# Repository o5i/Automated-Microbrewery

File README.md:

# Automated-Microbrewery

This is a small hobby/micro brewery based on herms system. i have created for friends.
The setup appart of the work i spend has a good price/quality value. 
In all i spent about 800€ for the hardware.
The controller is made of a raspberry pi (debian linux) interfaced whit a Teensy (Arduino based Microcontroller). 
The program runs on codesys, codesys is a  IEC 61131-3 runtime that allows me to use standard plc programing languages. 
I decided to use the pi because it is possible to interface whit a lot of cheap hardware like the multitouch screen.
The other point is that you have access to the network/internet and you can implement a webinterface or other remote management.
The controller box is made from lasercutted wood.
The gas burners came from old wrecked gas heaters.

Here you can see the controler in action:

https://www.youtube.com/watch?v=9Vse3HxLSbY

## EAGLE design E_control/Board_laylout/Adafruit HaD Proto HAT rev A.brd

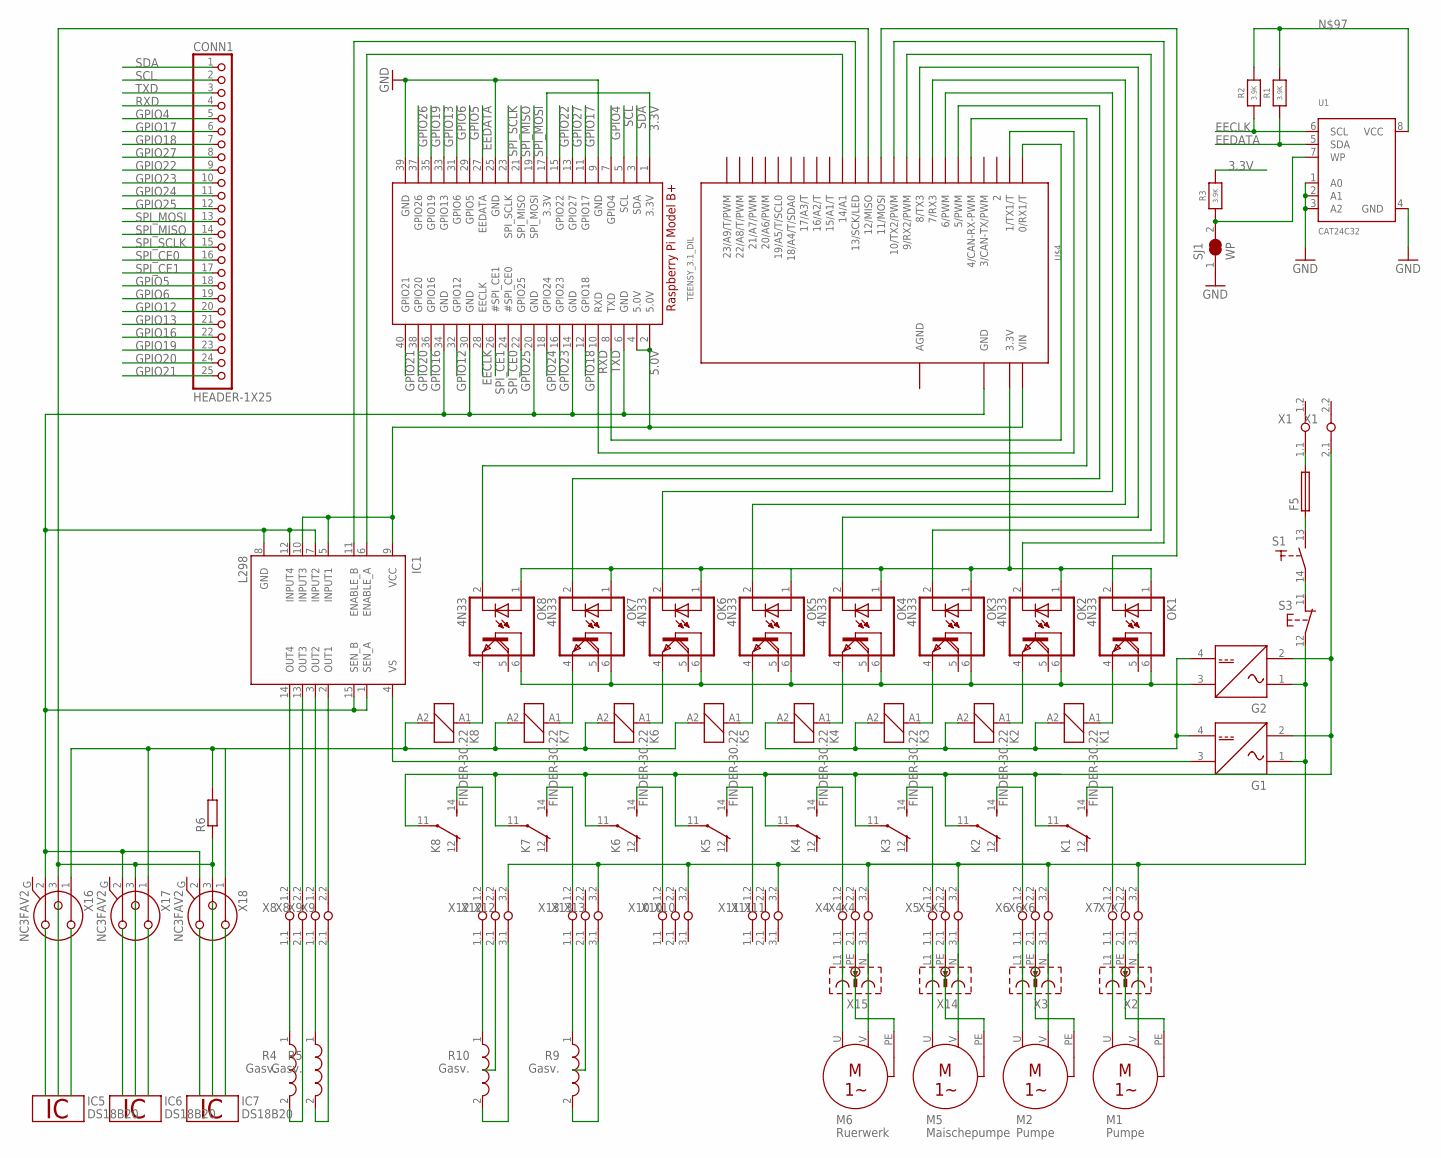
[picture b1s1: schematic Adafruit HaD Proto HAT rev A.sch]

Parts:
CONN1: HEADER-1X25; 1X25_ROUND_70MIL
F5: KS9V
G1, G2: NETZTEIL_GLEICHSPANNUNG
IC1: L298; MULTIWATT-15
IC5, IC6, IC7: DS18B20; TO92-
K1, K2, K3, K4, K5, K6, K7, K8: FINDER-30.22
M1, M2: Pumpe; MOTOR_1-PHASEN
M5: Maischepumpe; MOTOR_1-PHASEN
M6: Ruerwerk; MOTOR_1-PHASEN
OK1, OK2, OK3, OK4, OK5, OK6, OK7, OK8: 4N33; DIL06
R1, R2, R3: 3.9K; 0805-NO
R4, R5, R9, R10: Gasv.; SPULE
R6: R-EU_0204/2V; 0204V
RPI1: RASPBERRYPI_BPLUS_HATNOSLOTS; PI_HAT_NOSLOTS
S1: SCHLIESSER_KIPPSCHALTER
S3: TASTER_OEFFNER; AUSTASTER
SJ1: WP; SOLDERJUMPER_CLOSEDWIRE
U1: CAT24C32; SOIC8_150MIL
U$4: TEENSY_3.1_DIL; TEENSY3-DIL
X1, X8, X9: KLEMME_1-2
X2, X3, X14, X15: STECKDOSE
X4, X5, X6, X7, X10, X11, X12, X13: KLEMME_1-3
X16, X17, X18: NC3FAV2

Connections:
1W: IC5.2 (1W), IC6.2 (1W), IC7.2 (1W)
3.3V: R3.2, RPI1.1 (3.3V), RPI1.17 (3.3V)
5.0V: IC1.5 (INPUT1), IC1.9 (VCC), IC1.10 (INPUT3), RPI1.2 (5.0V), RPI1.4 (5.0V), U$4.VIN
AGND: U$4.AGND
EECLK: R2.1, RPI1.28 (EECLK), U1.6 (SCL)
EEDATA: R1.1, RPI1.27 (EEDATA), U1.5 (SDA)
GND: IC1.1 (SEN_A), IC1.7 (INPUT2), IC1.8 (GND), IC1.12 (INPUT4), IC1.15 (SEN_B), IC5.1 (GND), IC6.1 (GND), IC7.1 (GND), RPI1.6 (GND), RPI1.9 (GND), RPI1.14 (GND), RPI1.20 (GND), RPI1.25 (GND), RPI1.30 (GND), RPI1.34 (GND), RPI1.39 (GND), SJ1.1, U1.1 (A0), U1.2 (A1), U1.3 (A2), U1.4 (GND), U$4.GND, X16.2, X17.2, X18.2
GPIO4: CONN1.5, RPI1.7 (GPIO4)
GPIO5: CONN1.18, RPI1.29 (GPIO5)
GPIO6: CONN1.19, RPI1.31 (GPIO6)
GPIO12: CONN1.20, RPI1.32 (GPIO12)
GPIO13: CONN1.21, RPI1.33 (GPIO13)
GPIO16: CONN1.22, RPI1.36 (GPIO16)
GPIO17: CONN1.6, RPI1.11 (GPIO17)
GPIO18: CONN1.7, RPI1.12 (GPIO18)
GPIO19: CONN1.23, RPI1.35 (GPIO19)
GPIO20: CONN1.24, RPI1.38 (GPIO20)
GPIO21: CONN1.25, RPI1.40 (GPIO21)
GPIO22: CONN1.9, RPI1.15 (GPIO22)
GPIO23: CONN1.10, RPI1.16 (GPIO23)
GPIO24: CONN1.11, RPI1.18 (GPIO24)
GPIO25: CONN1.12, RPI1.22 (GPIO25)
GPIO26: RPI1.37 (GPIO26)
GPIO27: CONN1.8, RPI1.13 (GPIO27)
unnamed: R3.1, SJ1.2, U1.7 (WP)
unnamed: IC1.11 (ENABLE_B), U$4.13 (13/SCK/LED)
unnamed: IC1.6 (ENABLE_A), U$4.14/A0 (14/A1)
unnamed: IC1.14 (OUT4), X8.1.2
unnamed: G1.3, IC1.4 (VS)
unnamed: G1.1, G1.2, G2.1, G2.2, S3.12 (2), X1.2.1, X4.3.2, X5.3.2, X6.3.2, X7.3.2, X10.3.2, X11.3.2, X12.3.2, X13.3.2
unnamed: R4.2, X8.2.1
unnamed: IC1.3 (OUT2), X9.1.2
unnamed: IC1.2 (OUT1), X9.2.2
unnamed: IC1.13 (OUT3), X8.2.2
unnamed: OK4.2 (C), U$4.8 (8/TX3)
unnamed: OK3.2 (C), U$4.9 (9/RX2/PWM)
unnamed: OK2.2 (C), U$4.10 (10/TX2/PWM)
unnamed: OK1.2 (C), U$4.11 (11/MOSI)
unnamed: G2.3, OK1.6 (B), OK2.6 (B), OK3.6 (B), OK4.6 (B), OK5.6 (B), OK6.6 (B), OK7.6 (B), OK8.6 (B)
unnamed: K1.A1 (1), OK1.4 (E)
unnamed: K2.A1 (1), OK2.4 (E)
unnamed: K3.A1 (1), OK3.4 (E)
unnamed: K4.A1 (1), OK4.4 (E)
unnamed: M1.U, X2.L1, X7.1.1
unnamed: M2.U, X3.L1, X6.1.1
unnamed: K3.14 (S), X5.1.2
unnamed: K4.14 (S), X4.1.2
unnamed: M5.U, X5.1.1, X14.L1
unnamed: M6.U, X4.1.1, X15.L1
unnamed: K2.14 (S), X6.1.2
unnamed: M2.V, X3.N, X6.3.1
unnamed: K1.14 (S), X7.1.2
unnamed: M1.V, X2.N, X7.3.1
unnamed: X3.PE, X6.2.1
unnamed: X2.PE, X7.2.1
unnamed: M6.V, X4.3.1, X15.N
unnamed: M5.V, X5.3.1, X14.N
unnamed: R4.1, X8.1.1
unnamed: F5.2, X1.1.1
unnamed: F5.1, S1.13 (3)
unnamed: S1.14 (4), S3.11 (1)
unnamed: R6.1, U$4.12 (12/MISO), X16.3, X17.3, X18.3
unnamed: G1.4, G2.4, K1.A2 (2), K2.A2 (2), K3.A2 (2), K4.A2 (2)
unnamed: OK8.2 (C), U$4.4 (4/CAN-RX-PWM)
unnamed: OK7.2 (C), U$4.5 (5/PWM)
unnamed: OK6.2 (C), U$4.6 (6/PWM)
unnamed: OK5.2 (C), U$4.7 (7/RX3)
unnamed: R1.2, R2.2, U1.8 (VCC)
unnamed: K5.A1 (1), OK5.4 (E)
unnamed: K6.A1 (1), OK6.4 (E)
unnamed: K7.A1 (1), OK7.4 (E)
unnamed: K8.A1 (1), OK8.4 (E)
unnamed: R5.1, X9.1.1
unnamed: R5.2, X9.2.1
unnamed: K7.14 (S), X13.1.2
unnamed: K8.14 (S), X12.1.2
unnamed: K5.A2 (2), K6.A2 (2), K7.A2 (2), K8.A2 (2), R6.2, X16.1, X17.1, X18.1
unnamed: R9.1, X13.1.1
unnamed: R9.2, X13.3.1
unnamed: R10.2, X12.3.1
unnamed: R10.1, X12.1.1
unnamed: K6.14 (S), X10.1.2
unnamed: K5.14 (S), X11.1.2
unnamed: X4.2.1, X15.PE
unnamed: X5.2.1, X14.PE
unnamed: OK1.1 (A), OK2.1 (A), OK3.1 (A), OK4.1 (A), OK5.1 (A), OK6.1 (A), OK7.1 (A), OK8.1 (A), U$4.3.3V
RXD: CONN1.4, RPI1.10 (RXD), U$4.1 (1/TX1/T)
SCL: CONN1.2, RPI1.5 (SCL)
SDA: CONN1.1, RPI1.3 (SDA)
SPI_CE0: CONN1.16, RPI1.24 (#SPI_CE0)
SPI_CE1: CONN1.17, RPI1.26 (#SPI_CE1)
SPI_MISO: CONN1.14, RPI1.21 (SPI_MISO)
SPI_MOSI: CONN1.13, RPI1.19 (SPI_MOSI)
SPI_SCLK: CONN1.15, RPI1.23 (SPI_SCLK)
TXD: CONN1.3, RPI1.8 (TXD), U$4.0 (0/RX1/T)
VDD: IC5.3 (VDD), IC6.3 (VDD), IC7.3 (VDD)

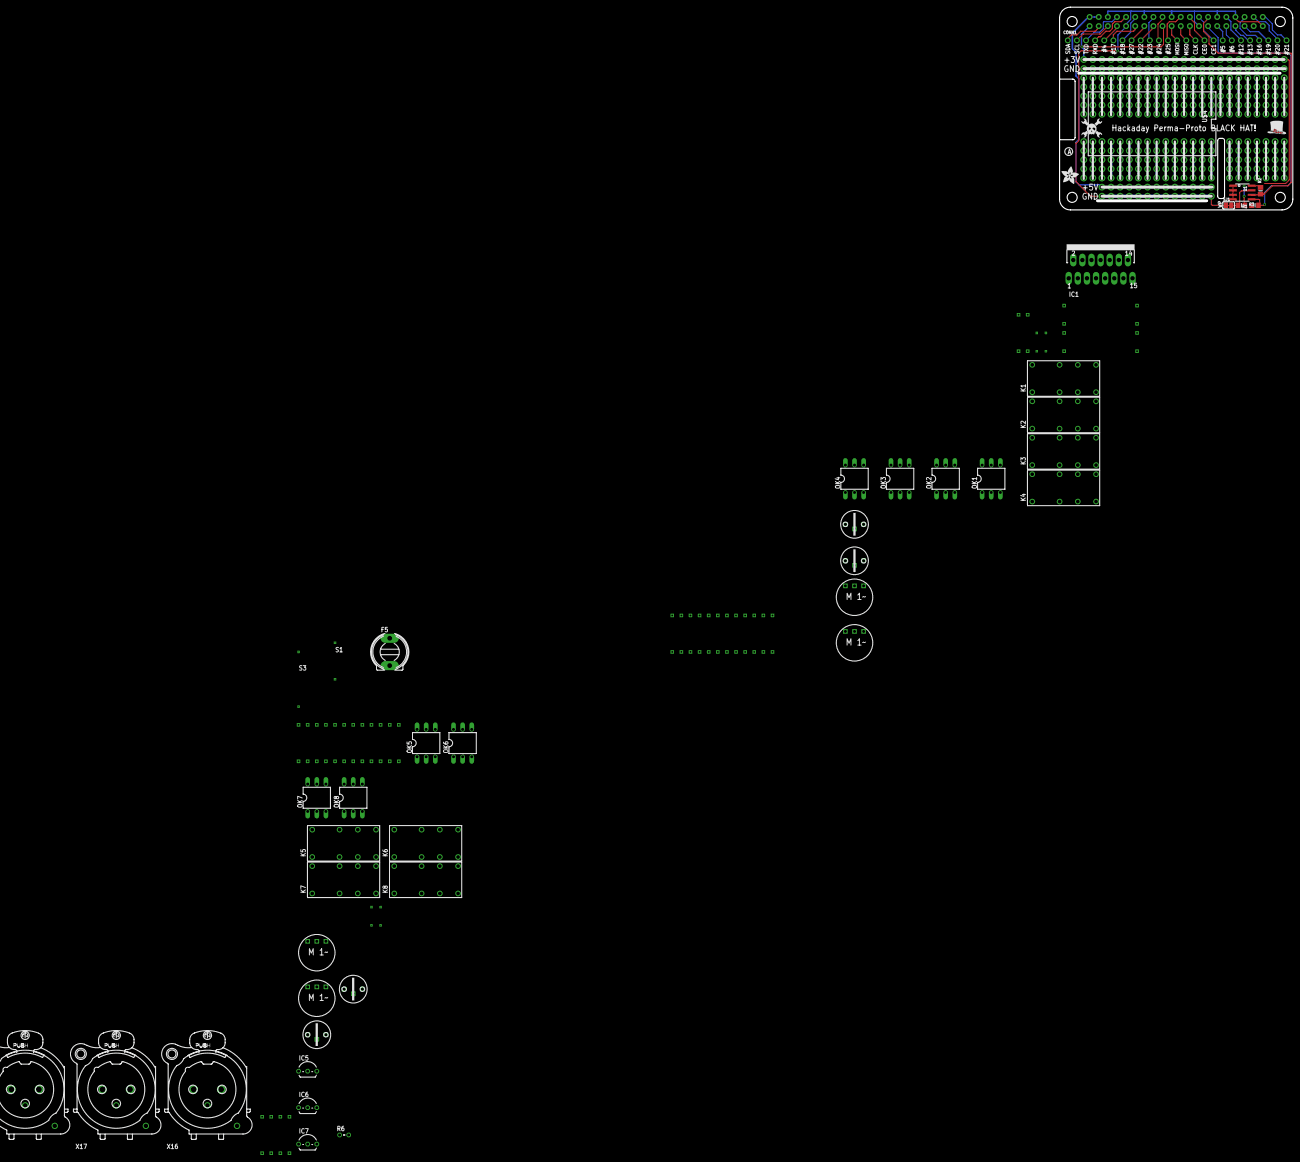
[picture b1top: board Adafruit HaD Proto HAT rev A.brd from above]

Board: 2 copper layers, 65.0 x 56.5 mm, 64 parts (0 on the bottom side), 94 nets.

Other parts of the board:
U$1: ADAFRUIT_5MM
U$2: PIHATLOGO
U$3: PCBFEAT-REV-056
U$5: HAD_LOGO_200MIL

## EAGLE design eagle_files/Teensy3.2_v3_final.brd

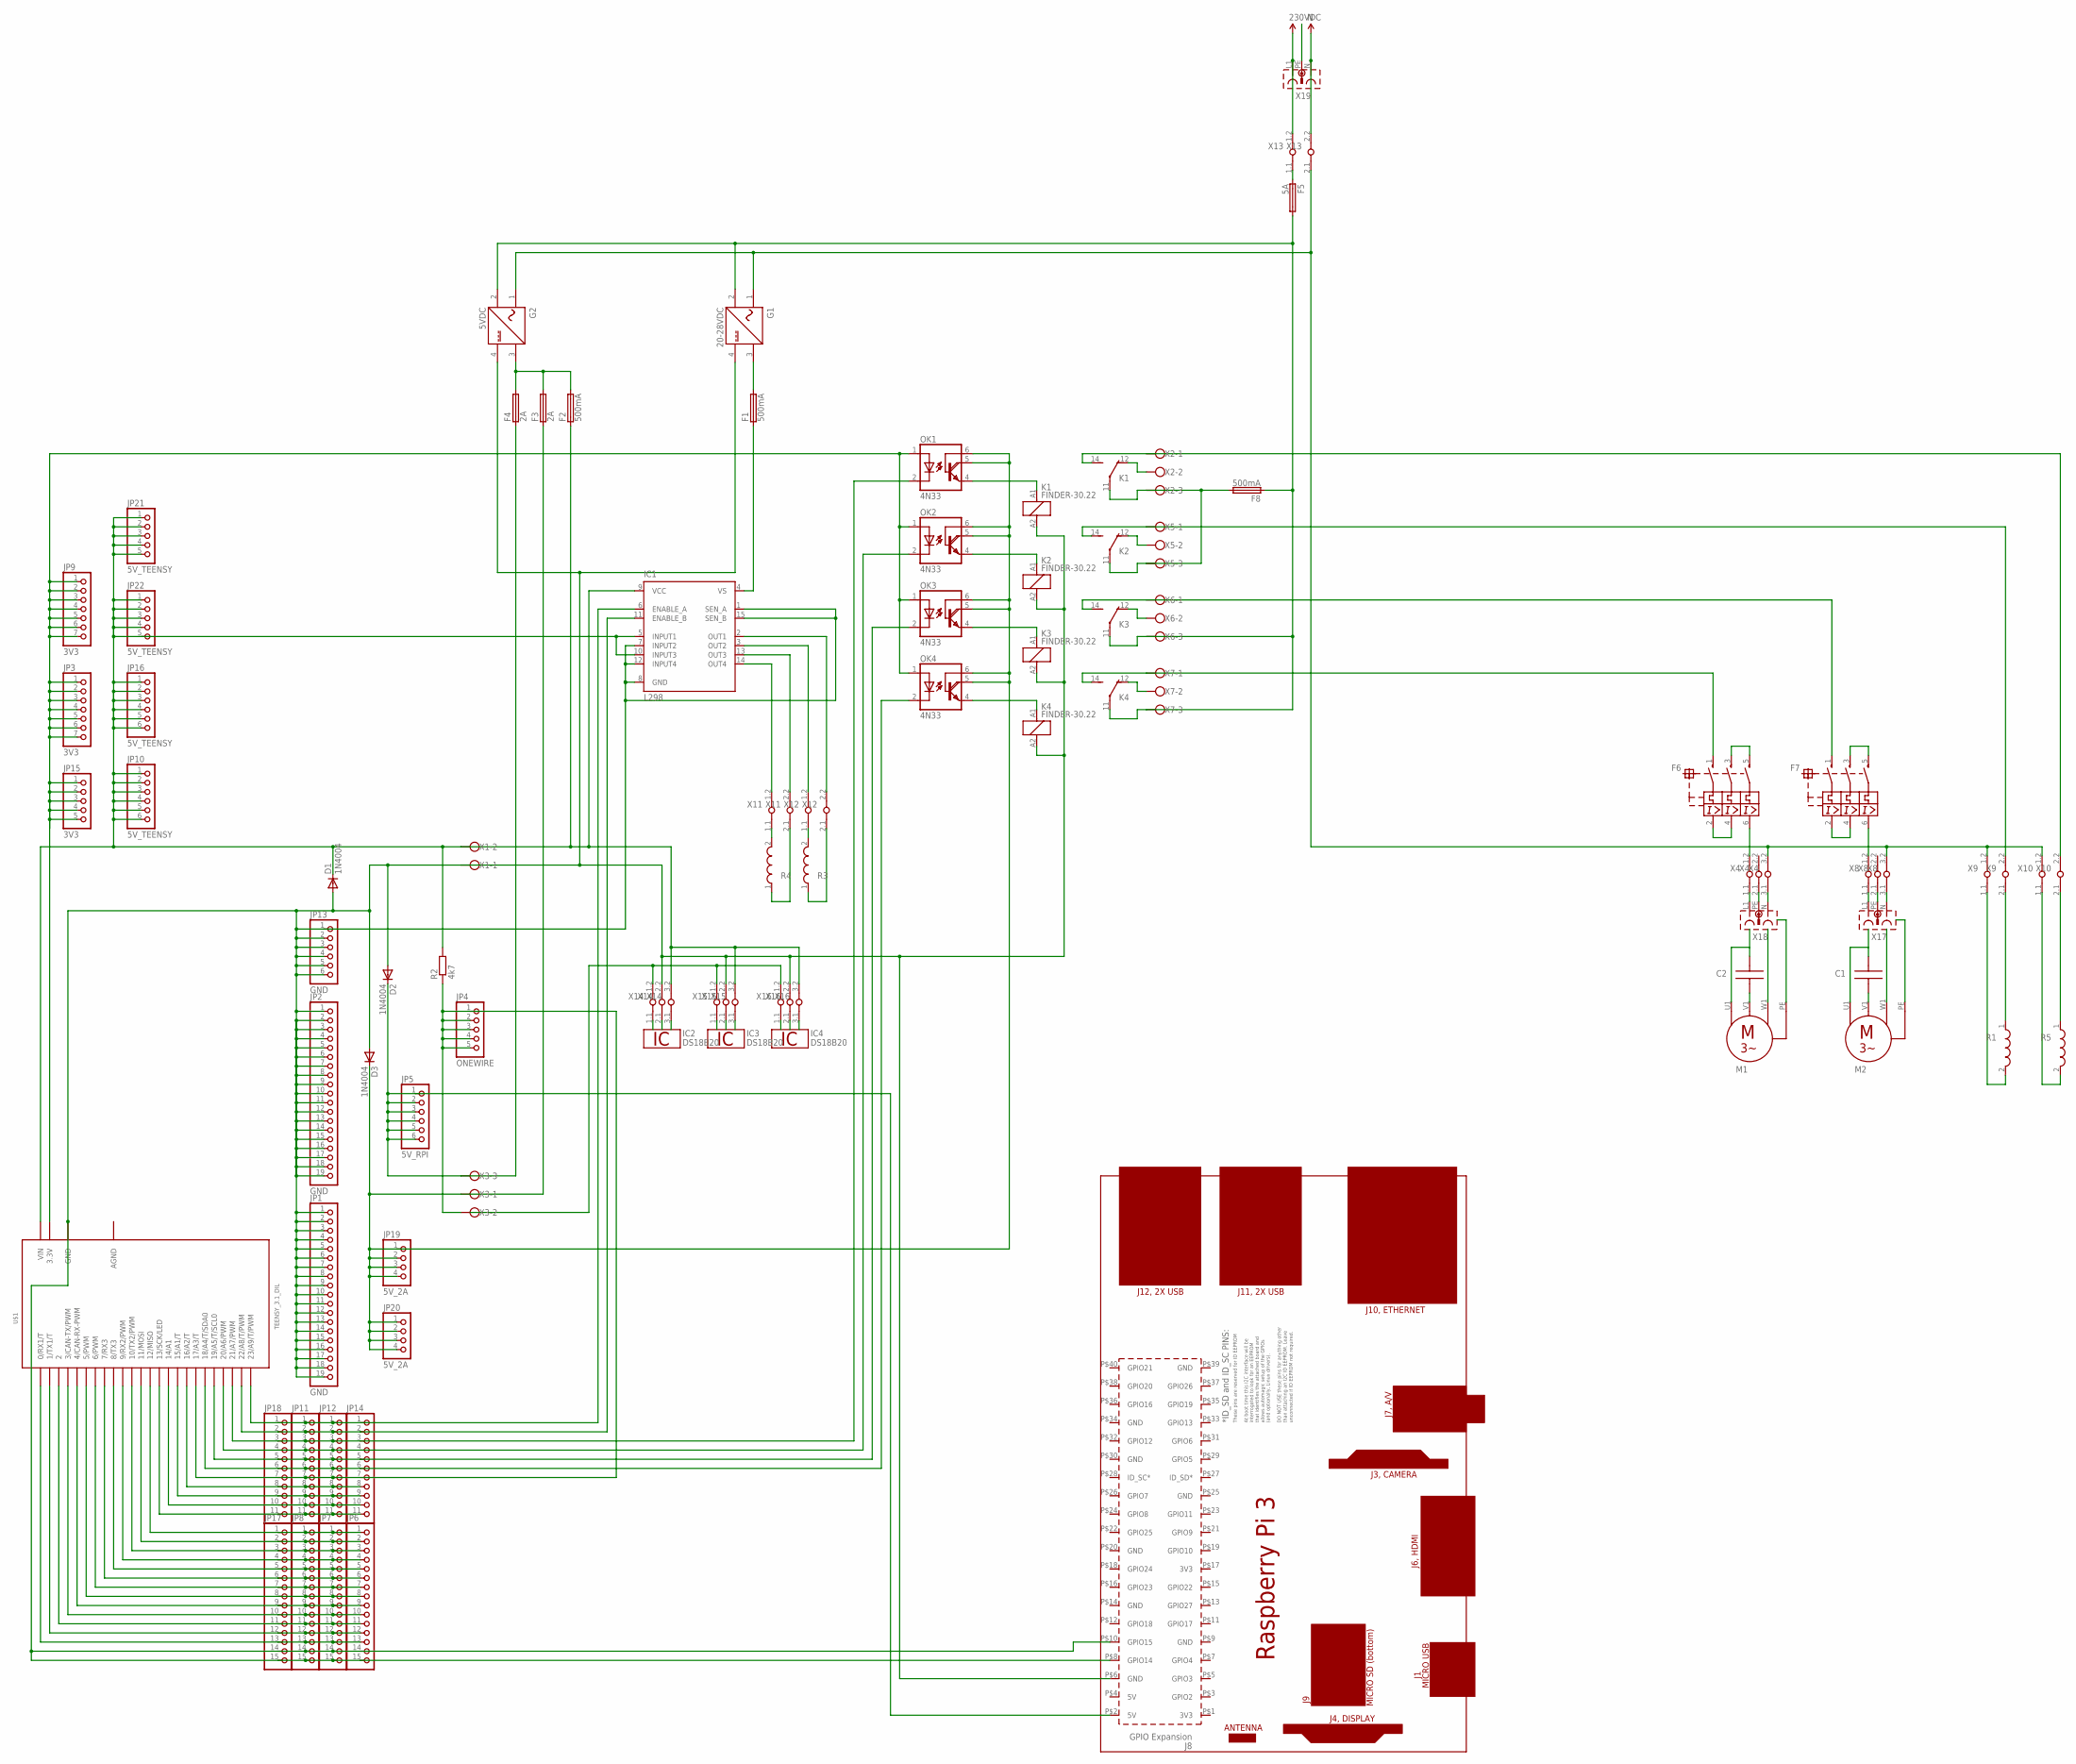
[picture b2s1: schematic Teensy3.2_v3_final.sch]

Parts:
C1, C2: KONDENSATOR_KAPAZITAET_ALLGEMEIN
D1, D2, D3: 1N4004; DO41-10
F1, F2, F8: 500mA; GSH15
F3, F4: 2A; GSH15
F5: 5A; GSH15
F6, F7: MOTORSCHUTZSCHALTER_3-POL_THERM_MAG_HANDBETAETIGT
G1: 20-28VDC; NETZTEIL_GLEICHSPANNUNG
G2: 5VDC; NETZTEIL_GLEICHSPANNUNG
IC1: L298; MULTIWATT-15
IC2, IC3, IC4: DS18B20; TO92-
JP1, JP2: GND; 1X19
JP3, JP9: 3V3; 1X07
JP4: ONEWIRE; 1X05
JP5: 5V_RPI; 1X06
JP6, JP7, JP8, JP17: PINHD-1X15; 1X15
JP10, JP16: 5V_TEENSY; 1X06
JP11, JP12, JP14, JP18: PINHD-1X11; 1X11
JP13: GND; 1X06
JP15: 3V3; 1X05
JP19, JP20: 5V_2A; 1X04
JP21, JP22: 5V_TEENSY; 1X05
K1, K2, K3, K4: FINDER-30.22
M1, M2: MOTOR_3-POL_PE
OK1, OK2, OK3, OK4: 4N33; DIL06
PCB1: RPI3
R1, R3, R4, R5: SPULE_ALTERNATIV; SPULE
R2: 4k7; 0204/5
U$1: TEENSY_3.1_DIL; TEENSY3-DIL
X1: W237-102
X2, X3, X5, X6, X7: W237-103
X4, X8, X14, X15, X16: KLEMME_1-3
X9, X10, X11, X12, X13: KLEMME_1-2
X17, X18, X19: STECKDOSE

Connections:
0V: D1.A, D2.A, D3.A, G1.4, G2.4, IC1.1 (SEN_A), IC1.7 (INPUT2), IC1.8 (GND), IC1.12 (INPUT4), IC1.15 (SEN_B), JP1.1, JP1.2, JP1.3, JP1.4, JP1.5, JP1.6, JP1.7, JP1.8, JP1.9, JP1.10, JP1.11, JP1.12, JP1.13, JP1.14, JP1.15, JP1.16, JP1.17, JP1.18, JP1.19, JP2.1, JP2.2, JP2.3, JP2.4, JP2.5, JP2.6, JP2.7, JP2.8, JP2.9, JP2.10, JP2.11, JP2.12, JP2.13, JP2.14, JP2.15, JP2.16, JP2.17, JP2.18, JP2.19, JP6.14, JP6.15, JP7.14, JP7.15, JP8.14, JP8.15, JP13.1, JP13.2, JP13.3, JP13.4, JP13.5, JP13.6, JP17.14, JP17.15, K1.A2 (2), K2.A2 (2), K3.A2 (2), K4.A2 (2), PCB1.P$6 (GND), PCB1.P$8 (GPIO14), PCB1.P$10 (GPIO15), U$1.GND, X1.1, X14.2.2, X15.2.2, X16.2.2
1W: IC2.2 (1W), IC3.2 (1W), IC4.2 (1W)
5V_0,5A: D1.C, F2.1, IC1.5 (INPUT1), IC1.9 (VCC), IC1.10 (INPUT3), JP10.1, JP10.2, JP10.3, JP10.4, JP10.5, JP10.6, JP16.1, JP16.2, JP16.3, JP16.4, JP16.5, JP16.6, JP21.1, JP21.2, JP21.3, JP21.4, JP21.5, JP22.1, JP22.2, JP22.3, JP22.4, JP22.5, R2.2, U$1.VIN, X1.2, X14.3.2, X15.3.2, X16.3.2
5V_1A: D3.C, F3.1, JP19.1, JP19.2, JP19.3, JP19.4, JP20.1, JP20.2, JP20.3, JP20.4, OK1.5 (COL), OK1.6 (B), OK2.5 (COL), OK2.6 (B), OK3.5 (COL), OK3.6 (B), OK4.5 (COL), OK4.6 (B), X3.1
5V_2A: D2.C, F4.1, JP5.1, JP5.2, JP5.3, JP5.4, JP5.5, JP5.6, PCB1.P$2 (5V), X3.3
AGND: U$1.AGND
GND: IC2.1 (GND), IC3.1 (GND), IC4.1 (GND)
unnamed: JP4.1, JP4.2, JP4.3, JP4.4, JP4.5, JP11.7, JP12.7, JP14.7, JP18.7, R2.1, U$1.17/A3 (17/A3/T), X3.2
unnamed: F8.2, K1.11, K2.11, X2.3, X5.3
unnamed: R4.2, X11.1.1
unnamed: JP6.13, JP7.13, JP8.13, JP17.13, U$1.0 (0/RX1/T)
unnamed: X14.1.2, X15.1.2, X16.1.2
unnamed: JP6.11, JP7.11, JP8.11, JP17.11, U$1.2
unnamed: JP6.10, JP7.10, JP8.10, JP17.10, U$1.3 (3/CAN-TX/PWM)
unnamed: JP6.9, JP7.9, JP8.9, JP17.9, U$1.4 (4/CAN-RX-PWM)
unnamed: JP6.8, JP7.8, JP8.8, JP17.8, U$1.5 (5/PWM)
unnamed: JP6.7, JP7.7, JP8.7, JP17.7, U$1.6 (6/PWM)
unnamed: JP6.6, JP7.6, JP8.6, JP17.6, U$1.7 (7/RX3)
unnamed: JP6.5, JP7.5, JP8.5, JP17.5, U$1.8 (8/TX3)
unnamed: JP6.4, JP7.4, JP8.4, JP17.4, U$1.9 (9/RX2/PWM)
unnamed: JP6.3, JP7.3, JP8.3, JP17.3, U$1.10 (10/TX2/PWM)
unnamed: JP6.2, JP7.2, JP8.2, JP17.2, U$1.11 (11/MOSI)
unnamed: R4.1, X11.2.1
unnamed: JP6.1, JP7.1, JP8.1, JP17.1, U$1.12 (12/MISO)
unnamed: JP11.11, JP12.11, JP14.11, JP18.11, U$1.13 (13/SCK/LED)
unnamed: JP11.10, JP12.10, JP14.10, JP18.10, U$1.14/A0 (14/A1)
unnamed: JP11.9, JP12.9, JP14.9, JP18.9, U$1.15/A1 (15/A1/T)
unnamed: JP11.8, JP12.8, JP14.8, JP18.8, U$1.16/A2 (16/A2/T)
unnamed: F1.2, G1.3
unnamed: JP11.6, JP12.6, JP14.6, JP18.6, OK4.2 (C), U$1.18/A4 (18/A4/T/SDA0)
unnamed: R3.2, X12.1.1
unnamed: JP11.5, JP12.5, JP14.5, JP18.5, OK3.2 (C), U$1.19/A5 (19/A5/T/SCL0)
unnamed: JP11.4, JP12.4, JP14.4, JP18.4, OK2.2 (C), U$1.20/A6 (20/A6/PWM)
unnamed: JP11.3, JP12.3, JP14.3, JP18.3, OK1.2 (C), U$1.21/A7 (21/A7/PWM)
unnamed: IC1.11 (ENABLE_B), JP11.2, JP12.2, JP14.2, JP18.2, U$1.22/A8 (22/A8/T/PWM)
unnamed: IC1.6 (ENABLE_A), JP11.1, JP12.1, JP14.1, JP18.1, U$1.23/A9 (23/A9/T/PWM)
unnamed: K1.A1 (1), OK1.4 (E)
unnamed: JP6.12, JP7.12, JP8.12, JP17.12, U$1.1 (1/TX1/T)
unnamed: JP3.1, JP3.2, JP3.3, JP3.4, JP3.5, JP3.6, JP3.7, JP9.1, JP9.2, JP9.3, JP9.4, JP9.5, JP9.6, JP9.7, JP15.1, JP15.2, JP15.3, JP15.4, JP15.5, OK1.1 (A), OK2.1 (A), OK3.1 (A), OK4.1 (A), U$1.3.3V
unnamed: R3.1, X12.2.1
unnamed: F5.1, X13.1.1
unnamed: K1.12 (O), X2.2
unnamed: F5.2, F8.1, G1.2, G2.2, K3.11, K4.11, X6.3, X7.3
unnamed: F6.2, F6.4
unnamed: K4.A1 (1), OK4.4 (E)
unnamed: K3.A1 (1), OK3.4 (E)
unnamed: K2.A1 (1), OK2.4 (E)
unnamed: F6.3, F6.5
unnamed: F6.6, X4.1.2
unnamed: F6.1, F7.1, K2.14 (S), X5.1, X9.2.2
unnamed: K2.12 (O), X5.2
unnamed: F7.2, F7.4
unnamed: K3.14 (S), X6.1
unnamed: K3.12 (O), X6.2
unnamed: F7.3, F7.5
unnamed: K4.14 (S), X7.1
unnamed: K4.12 (O), X7.2
unnamed: X4.1.1, X18.L1
unnamed: C2.2, M1.V1
unnamed: C1.2, M2.V1
unnamed: K1.14 (S), X2.1, X10.2.2
unnamed: C2.1, M1.U1
unnamed: X4.2.1, X18.PE
unnamed: C1.1, M2.U1
unnamed: X4.3.1, X18.N
unnamed: R1.2, X9.1.1
unnamed: R1.1, X9.2.1
unnamed: R5.2, X10.1.1
unnamed: R5.1, X10.2.1
unnamed: X8.3.1, X17.N
unnamed: X8.1.1, X17.L1
unnamed: IC1.13 (OUT3), X11.2.2
unnamed: IC1.2 (OUT1), X12.2.2
unnamed: G1.1, G2.1, X4.3.2, X8.3.2, X9.1.2, X10.1.2, X13.2.1
unnamed: F1.1, IC1.4 (VS)
unnamed: F2.2, F3.2, F4.2, G2.3
unnamed: F7.6, X8.1.2
unnamed: X8.2.1, X17.PE
VCC: X13.1.2, X13.2.2, X19.L1, X19.N
VDD: IC2.3 (VDD), IC3.3 (VDD), IC4.3 (VDD)

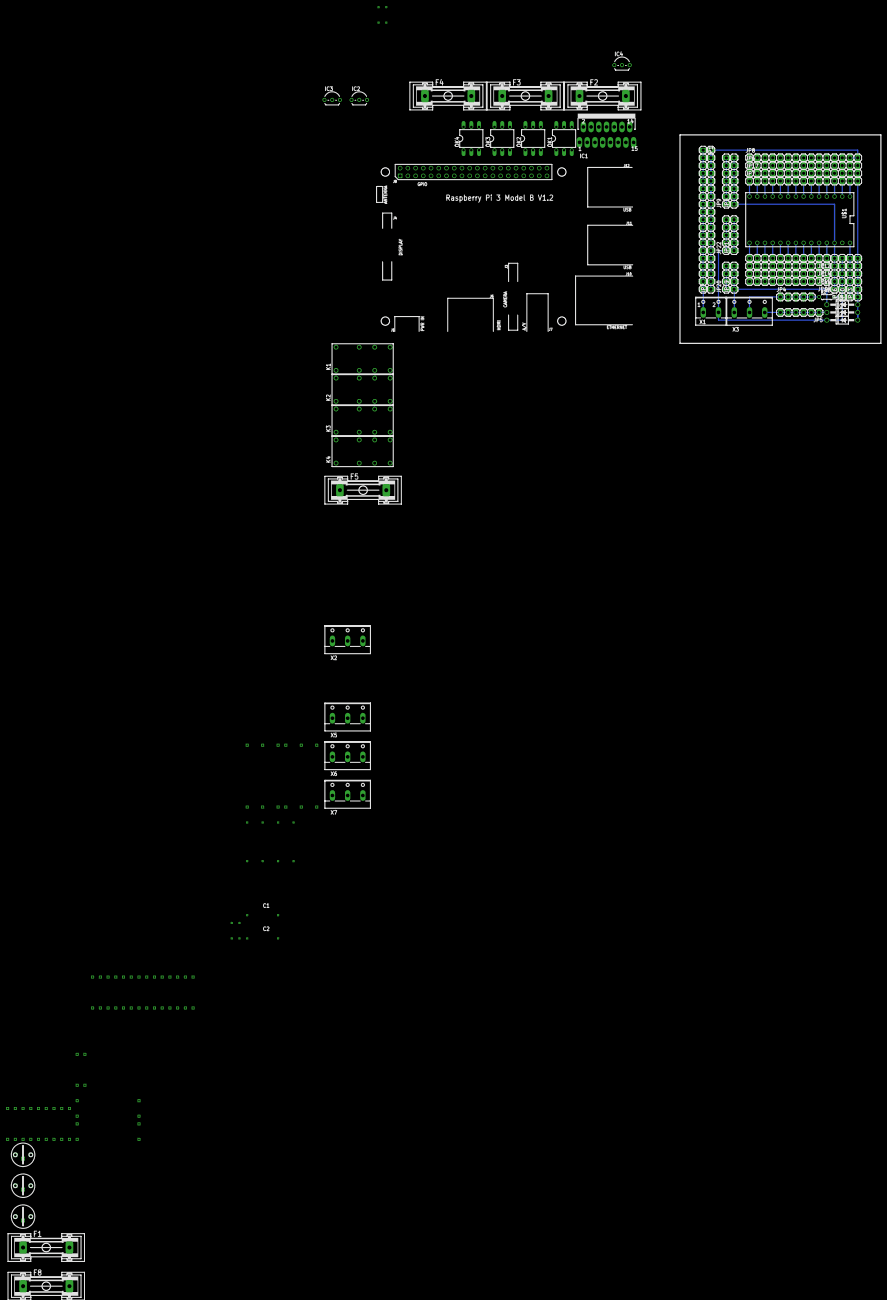
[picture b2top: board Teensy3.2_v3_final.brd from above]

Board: 2 copper layers, 66.0 x 68.5 mm, 77 parts (0 on the bottom side), 79 nets.

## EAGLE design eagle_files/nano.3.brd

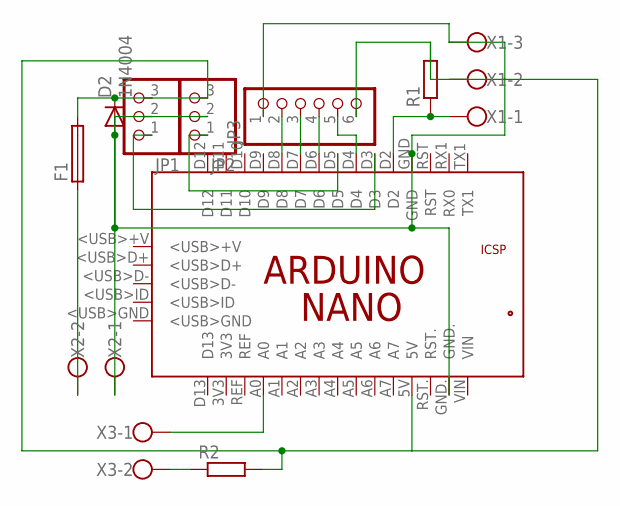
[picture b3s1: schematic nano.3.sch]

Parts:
D2: 1N4004; DO41-10
F1: GSH15
JP1, JP2: PINHD-1X3; 1X03
JP3: PINHD-1X6; 1X06
PCB2: ARDUINO_NANO
R1: R-EU_0207/15; 0207/15
R2: R-EU_0204/7; 0204/7
X1: W237-103
X2, X3: W237-102

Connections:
unnamed: D2.C, F1.2, JP1.3, JP2.3, JP3.6, PCB2.5V, R1.2, R2.2, X1.2
unnamed: D2.A, JP1.2, JP2.2, JP3.1, PCB2.GND, PCB2.GND., X1.3, X2.1
unnamed: R2.1, X3.2
unnamed: PCB2.A0, X3.1
unnamed: JP3.2, PCB2.D8
unnamed: JP3.3, PCB2.D7
unnamed: JP3.4, PCB2.D6
unnamed: JP3.5, PCB2.D4
unnamed: JP2.1, PCB2.D5
unnamed: PCB2.D2, R1.1, X1.1
unnamed: JP1.1, PCB2.D3
unnamed: F1.1, X2.2

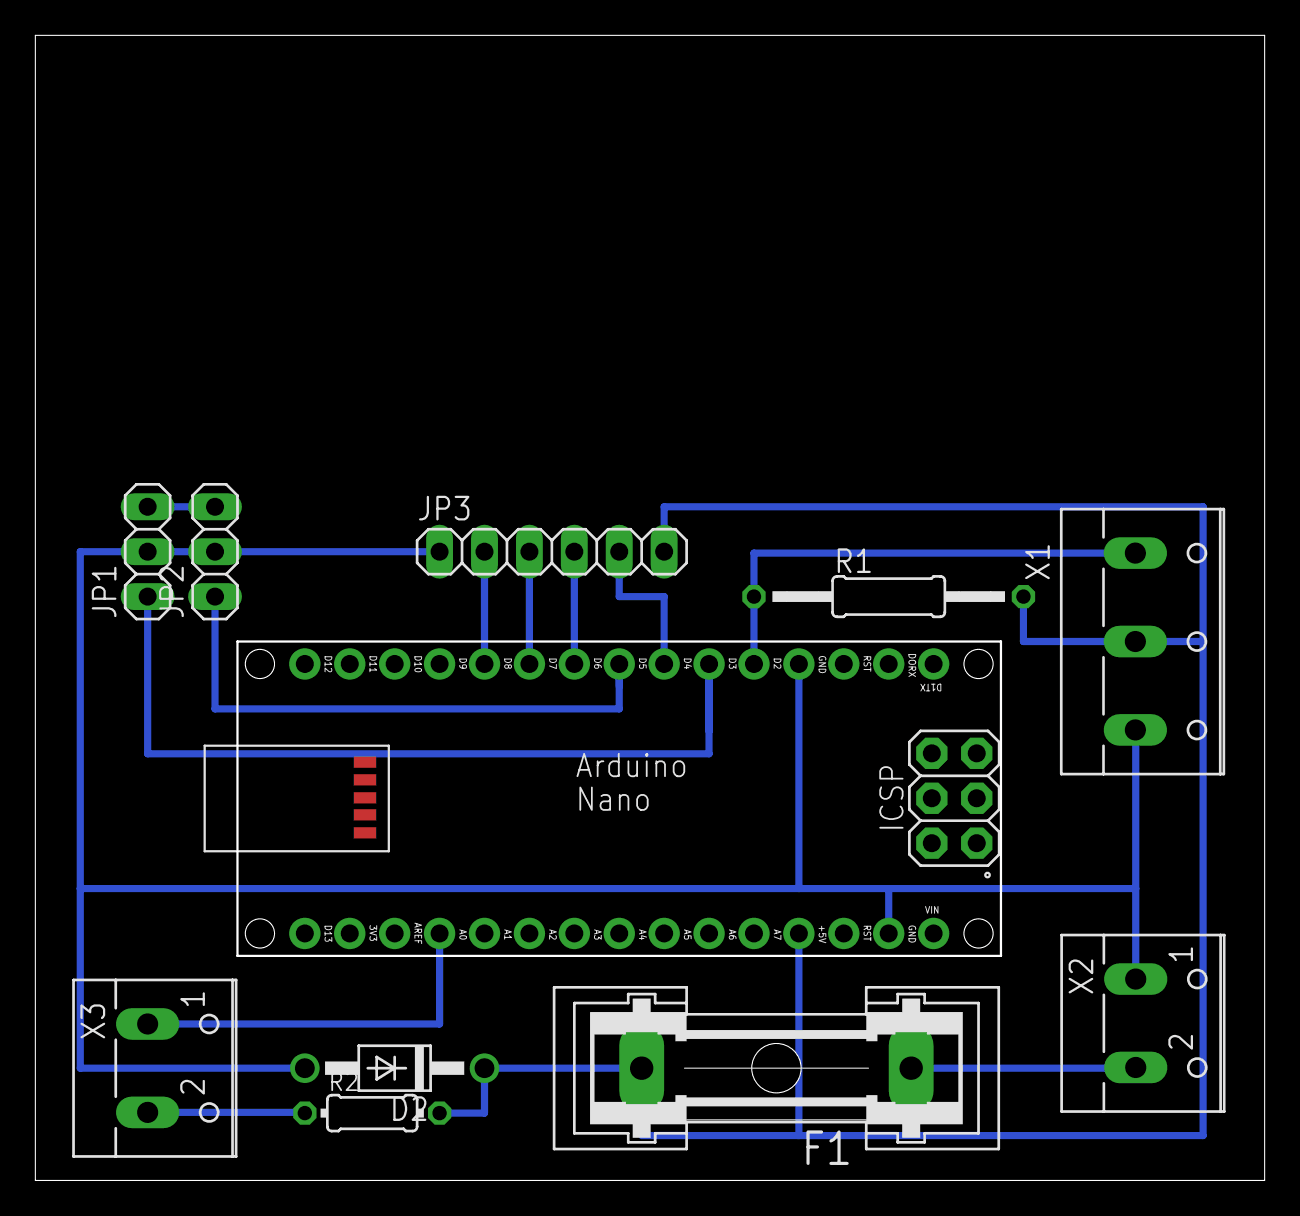
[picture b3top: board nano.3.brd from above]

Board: 2 copper layers, 69.5 x 64.8 mm, 11 parts (0 on the bottom side), 12 nets.

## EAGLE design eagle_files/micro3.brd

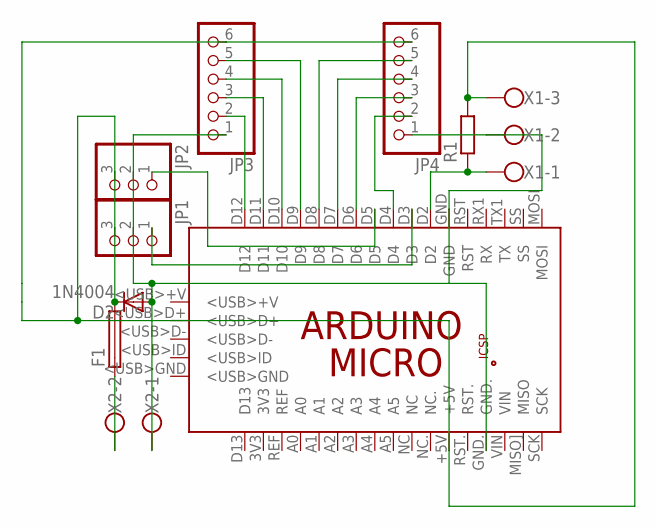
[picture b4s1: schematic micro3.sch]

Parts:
D2: 1N4004; DO41-10
F1: GSH15
JP1, JP2: PINHD-1X3; 1X03
JP3, JP4: PINHD-1X6; 1X06
PCB1: ARDUINO_MICRO
R1: R-EU_0207/15; 0207/15
X1: W237-103
X2: W237-102

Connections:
unnamed: JP3.2, PCB1.D12
unnamed: JP3.3, PCB1.D11
unnamed: JP3.4, PCB1.D10
unnamed: JP3.5, PCB1.D9
unnamed: JP4.5, PCB1.D8
unnamed: JP4.4, PCB1.D7
unnamed: JP4.3, PCB1.D6
unnamed: JP4.2, PCB1.D4
unnamed: JP2.1, PCB1.D5
unnamed: PCB1.D2, R1.1, X1.1
unnamed: JP1.1, PCB1.D3
unnamed: D2.C, F1.2, JP1.3, JP2.3, JP3.6, JP4.6, PCB1.+5V, R1.2, X1.3
unnamed: F1.1, X2.2
unnamed: D2.A, JP1.2, JP2.2, JP3.1, JP4.1, PCB1.GND, PCB1.GND., X1.2, X2.1

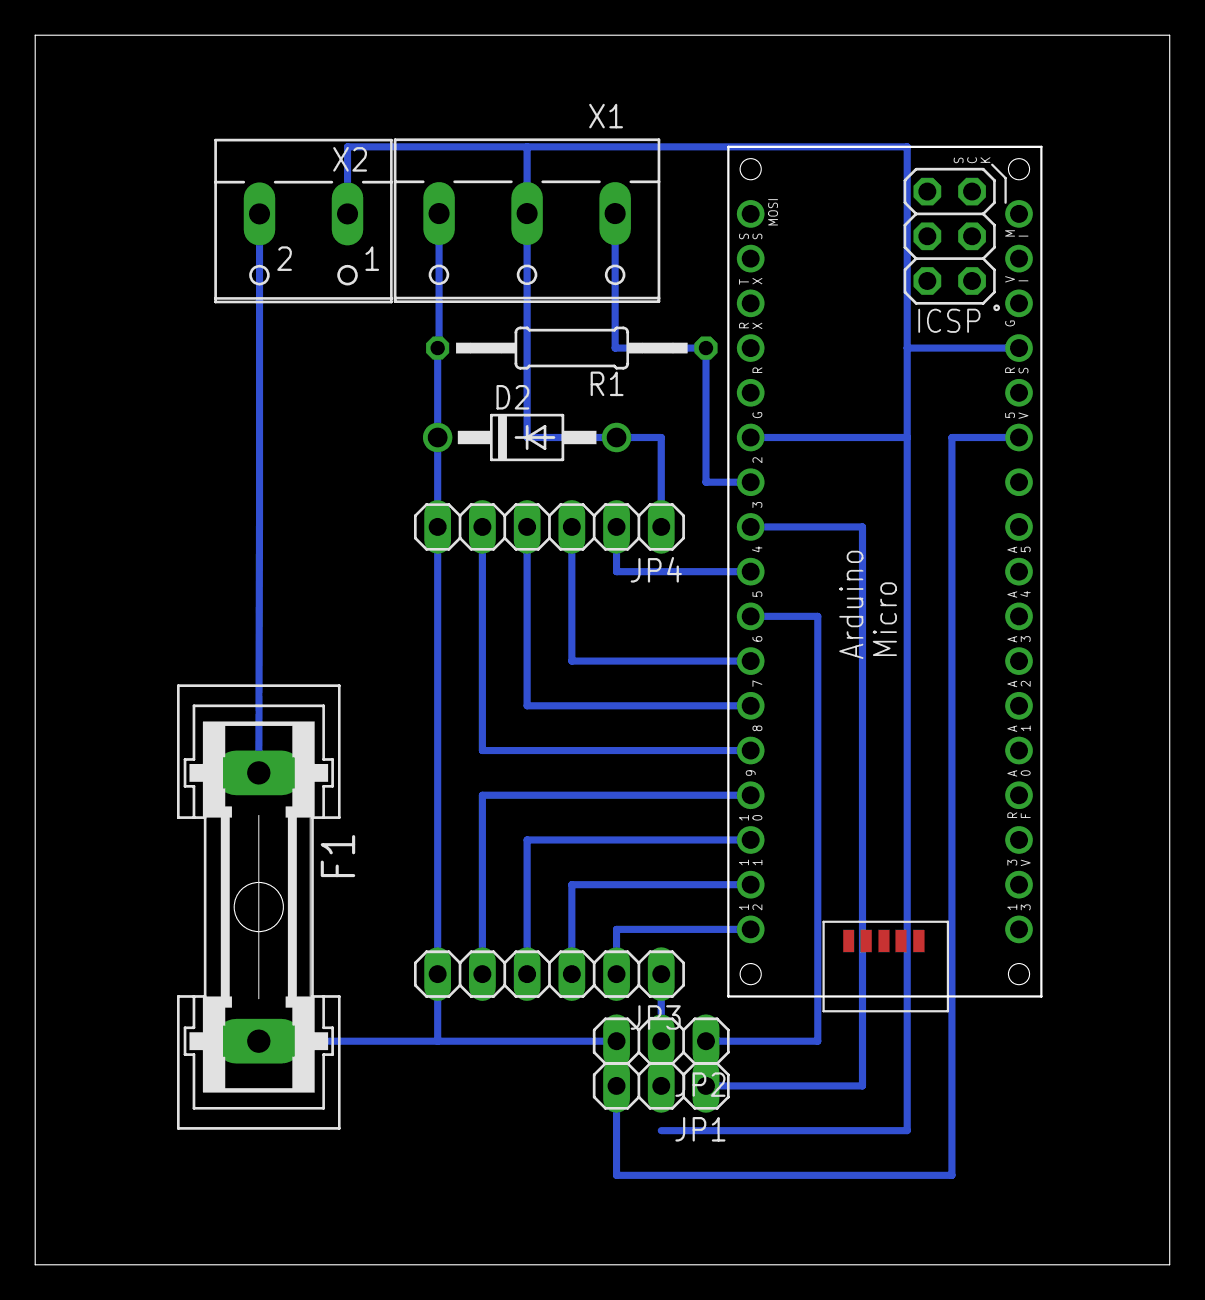
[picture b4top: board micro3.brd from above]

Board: 2 copper layers, 64.4 x 69.8 mm, 10 parts (0 on the bottom side), 14 nets.

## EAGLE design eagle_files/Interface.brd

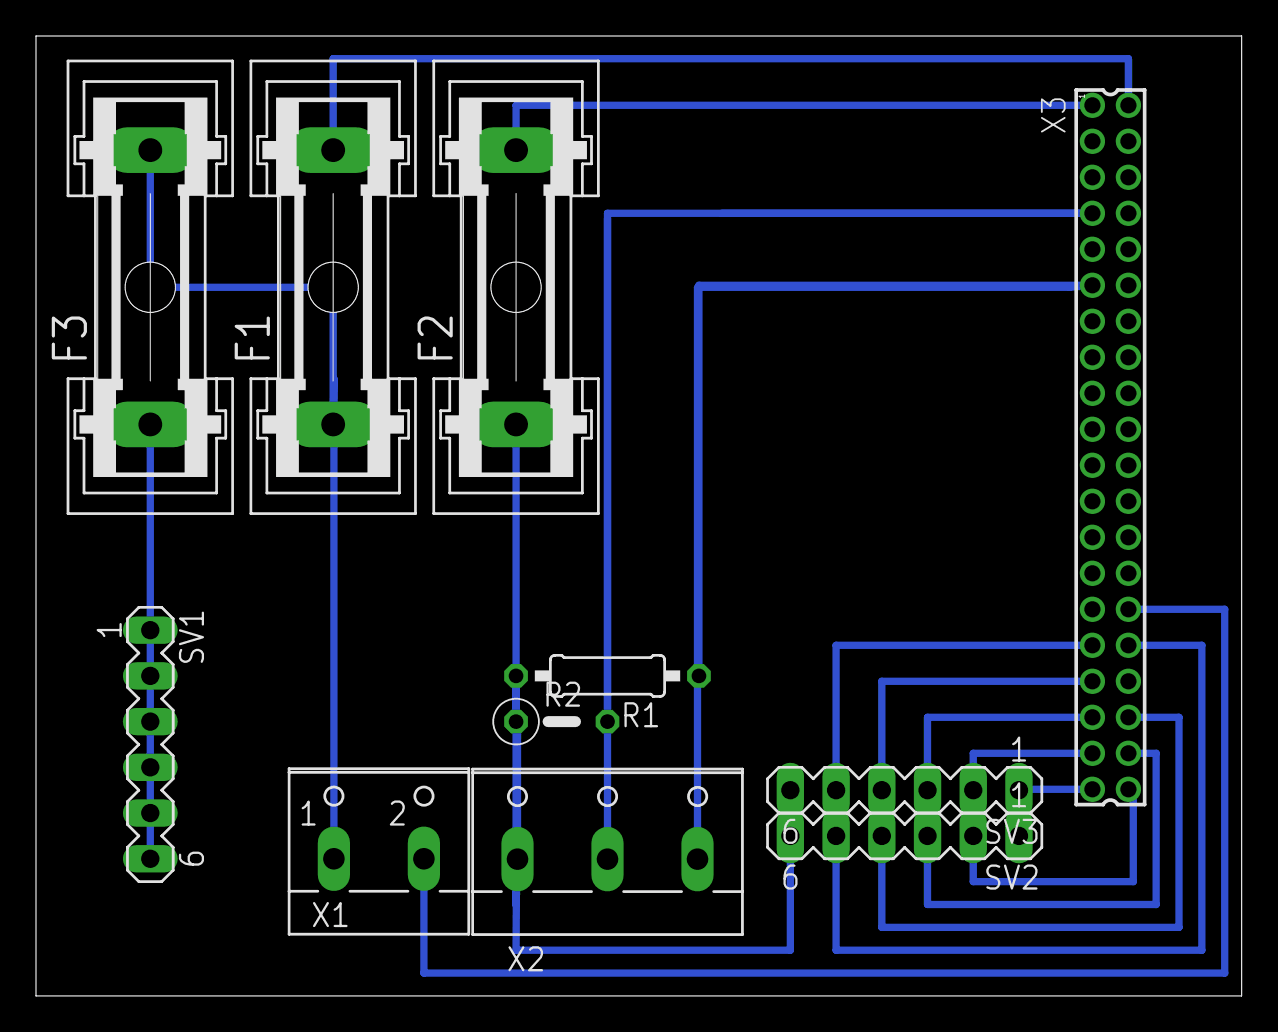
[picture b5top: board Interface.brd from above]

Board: 2 copper layers, 67.0 x 53.3 mm, 11 parts (0 on the bottom side), 17 nets.

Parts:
F1, F2, F3: GSH15
R1: 0207/10
R2: 0207/5V
SV1, SV2, SV3: MA06-1
X1: W237-102
X2: W237-103
X3: 87758-4016

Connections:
unnamed: F1.1, F3.2, X1.1
unnamed: F2.1, R1.2, R2.1, SV2.6, SV3.6, X2.1
unnamed: F3.1, SV1.6
unnamed: X1.2, X3.30
unnamed: R2.2, X2.2, X3.7
unnamed: R1.1, X2.3, X3.11
unnamed: SV2.5, X3.32
unnamed: SV2.4, X3.36
unnamed: SV2.3, X3.38
unnamed: SV2.2, X3.40
unnamed: SV3.2, X3.37
unnamed: SV3.3, X3.35
unnamed: SV3.4, X3.33
unnamed: SV3.5, X3.31
unnamed: F2.2, X3.1
unnamed: F1.2, X3.2
unnamed: SV2.1, SV3.1, X3.39

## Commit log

2016-08-15 :circus_tent: Added .gitattributes
2016-08-15 Version 0.0.1
2016-08-15 Addes some links
2016-08-15 change description
2016-08-16 added "confirmation to proceed" option on every cycle
2016-08-16 add eagle files
2016-08-16 change structure
2016-08-17 changed board layout
2016-08-17 some edit
2016-08-17 Update Teensyboard.ino
    added flame upper hysteresis
2016-08-17 added things to layout
2016-08-17 adafruit pi hat
2016-08-18 final circuit using rpi
2016-08-19 improve scematic
2016-08-19 image
2016-08-19 modified: Adafruit Hat/Adafruit HaD Proto HAT rev A.brd modified: Adafruit Hat/Adafruit HaD Proto HAT rev A.sch modified: Adafruit Hat/circuit.png modified: Adafruit Hat/eagle.epf
2016-08-19 new version
2016-08-20 some update
2016-08-20 modified: Arduino/Teensyboard0.3/Teensyboard0.3.ino
2016-08-21 edit & first test
2016-08-21 some changes
2016-08-22 added some changes
2016-08-24 Modbus Library Specs
2016-09-12 debuging
2016-09-12 Revert "debuging"
    This reverts commit 3dc7a87a9ffd4770db98203e23c44e083c265fd4.
    # Conflicts:
    # Arduino/Debug/Debug.ino
    # Arduino/Debug/Debug.ino.hex
2016-09-12 asdsadasdasRevert "debuging"
    This reverts commit 3dc7a87a9ffd4770db98203e23c44e083c265fd4.
2016-09-12 Revert "Update Teensyboard0.5.ino"
    This reverts commit 70fae832860cdd7d70b945816dcdc94eb0f86ffe.
2016-09-12 lalalal
2016-09-12 aaaaaaaaaaaaaaaaaaaaaaaa
2016-09-13 aaaaasdsadasd
    aaa
2016-09-13 sdasdasdasdas
2016-09-15 Added Grillmodeonly
2016-09-15 edit structure
2016-09-16 Moved to git
2016-09-16 cleanup
2016-09-16 montageplatte cad
2016-10-01 new box design
2020-06-08 updated to new codesys version

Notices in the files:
parts and their libraries:
microbuilder: This work is placed in the public domain, and may be freely used for commercial and non-commercial work with the following conditions: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
SparkFun-Aesthetics: Licensing: Creative Commons ShareAlike 4.0 International - https://creativecommons.org/licenses/by-sa/4.0
